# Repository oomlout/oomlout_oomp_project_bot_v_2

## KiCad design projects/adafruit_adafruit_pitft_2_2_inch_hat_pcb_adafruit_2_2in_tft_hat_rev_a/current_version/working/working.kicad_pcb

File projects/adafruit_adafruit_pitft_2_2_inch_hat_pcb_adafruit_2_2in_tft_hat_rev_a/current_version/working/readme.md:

# adafruit_pitft_2_2_inch_hat_pcb
 
## summary 
* id: adafruit_adafruit_pitft_2_2_inch_hat_pcb_adafruit_2_2in_tft_hat_rev_a
* user: adafruit
* name: adafruit_pitft_2_2_inch_hat_pcb
* board: adafruit_2_2in_tft_hat_rev_a
* repo: https://github.com/adafruit/Adafruit-PiTFT-2.2-Inch-HAT-PCB

* src_file_repo_sch: 
* src_file_repo_sch_link: https://github.com/adafruit/Adafruit-PiTFT-2.2-Inch-HAT-PCB/tree/master/
* full details link: https://github.com/oomlout/oomlout_oomp_project_bot_v_2/tree/main/projects/adafruit_adafruit_pitft_2_2_inch_hat_pcb_adafruit_2_2in_tft_hat_rev_a/current_version/working  

## schematic  
  
[schematic (pdf)](working_schematic.pdf) 

## pcb  

[board (pdf)](working.pdf)  

## working_bom
| Id | Designator | Footprint | Quantity | Designation | Supplier and ref |  | None | 
| --- | --- | --- | --- | --- | --- | --- | --- | 
| 1 | IC5 | SOT23 | 1 | AXP803 |  |  | [''] | 
| 2 | SW3,SW4,SW2,SW1 | EVQ-Q2 | 4 | SPST_TACT-EVQQ2 |  |  | [''] | 
| 3 | R2,R1,R3 | 0805-NO | 3 | 3.9K |  |  | [''] | 
| 4 | R10,R9 | 0805-NO | 2 | 1K |  |  | [''] | 
| 5 | U1 | SOIC8_150MIL | 1 | CAT24C32 |  |  | [''] | 
| 6 | RPI1 | PI_HAT_NOSLOTS | 1 | RASPBERRYPI_BPLUS_HATNOSLOTS |  |  | [''] | 
| 7 | R8,R5,R7,R4 | 0805-NO | 4 | 100 |  |  | [''] | 
| 8 | FID3,FID1,FID2 | FIDUCIAL_1MM | 3 | FIDUCIAL" |  |  | [''] | 
| 9 | U$4 | PIHATLOGO | 1 |  |  |  | [''] | 
| 10 | R6 | 0805-NO | 1 | 10K |  |  | [''] | 
| 11 | Q1 | SOT23-BEC | 1 | MMBT2222 |  |  | [''] | 
| 12 | CONN1 | 1X25_ROUND_70MIL | 1 | HEADER-1X25 |  |  | [''] | 
| 13 | U$1 | ADAFRUIT_5MM | 1 |  |  |  | [''] | 
| 14 | U2 | TM022HDH26_2.2IN_LCD | 1 | 2.2TFT |  |  | [''] | 
| 15 | U$12 | PCBFEAT-REV-056 | 1 |  |  |  | [''] | 
| 16 | SJ2 | SOLDERJUMPER_CLOSEDWIRE | 1 | BACKLITE |  |  | [''] | 
| 17 | SJ1 | SOLDERJUMPER_CLOSEDWIRE | 1 | WP |  |  | [''] | 
| 18 | U$3 | ADAFRUIT_TEXT_20MM | 1 |  |  |  | [''] | 

## bom_schematic
| Ref | Qnty | Value | Cmp name | Footprint | Description | Vendor | DNP | 
| --- | --- | --- | --- | --- | --- | --- | --- | 
| CONN1 | 1 | HEADER-1X25 | HEADER-1X25 | working:1X25_ROUND_70MIL |  |  |  | 
| FID1, FID2, FID3 | 3 | FIDUCIAL"" | FIDUCIAL{dblquote}{dblquote} | working:FIDUCIAL_1MM |  |  |  | 
| IC5 | 1 | AXP803 | AXP083-SAG | working:SOT23 |  |  |  | 
| Q1 | 1 | MMBT2222 | -NPN-SOT23-BEC | working:SOT23-BEC |  |  |  | 
| R1, R2, R3 | 3 | 3.9K | RESISTOR0805_NOOUTLINE | working:0805-NO |  |  |  | 
| R4, R5, R7, R8 | 4 | 100 | RESISTOR0805_NOOUTLINE | working:0805-NO |  |  |  | 
| R6 | 1 | 10K | RESISTOR0805_NOOUTLINE | working:0805-NO |  |  |  | 
| R9, R10 | 2 | 1K | RESISTOR0805_NOOUTLINE | working:0805-NO |  |  |  | 
| RPI1 | 1 | RASPBERRYPI_BPLUS_HATNOSLOTS | RASPBERRYPI_BPLUS_HATNOSLOTS | working:PI_HAT_NOSLOTS |  |  |  | 
| SJ1 | 1 | WP | SOLDERJUMPER_CLOSED | working:SOLDERJUMPER_CLOSEDWIRE |  |  |  | 
| SJ2 | 1 | BACKLITE | SOLDERJUMPERCLOSED | working:SOLDERJUMPER_CLOSEDWIRE |  |  |  | 
| SW1, SW2, SW3, SW4 | 4 | SPST_TACT-EVQQ2 | SPST_TACT-EVQQ2 | working:EVQ-Q2 |  |  |  | 
| U1 | 1 | CAT24C32 | EEPROM_I2C_SOIC8_GENERIC | working:SOIC8_150MIL |  |  |  | 
| U2 | 1 | 2.2TFT | DISP_LCD_TM022HDH26 | working:TM022HDH26_2.2IN_LCD |  |  |  |

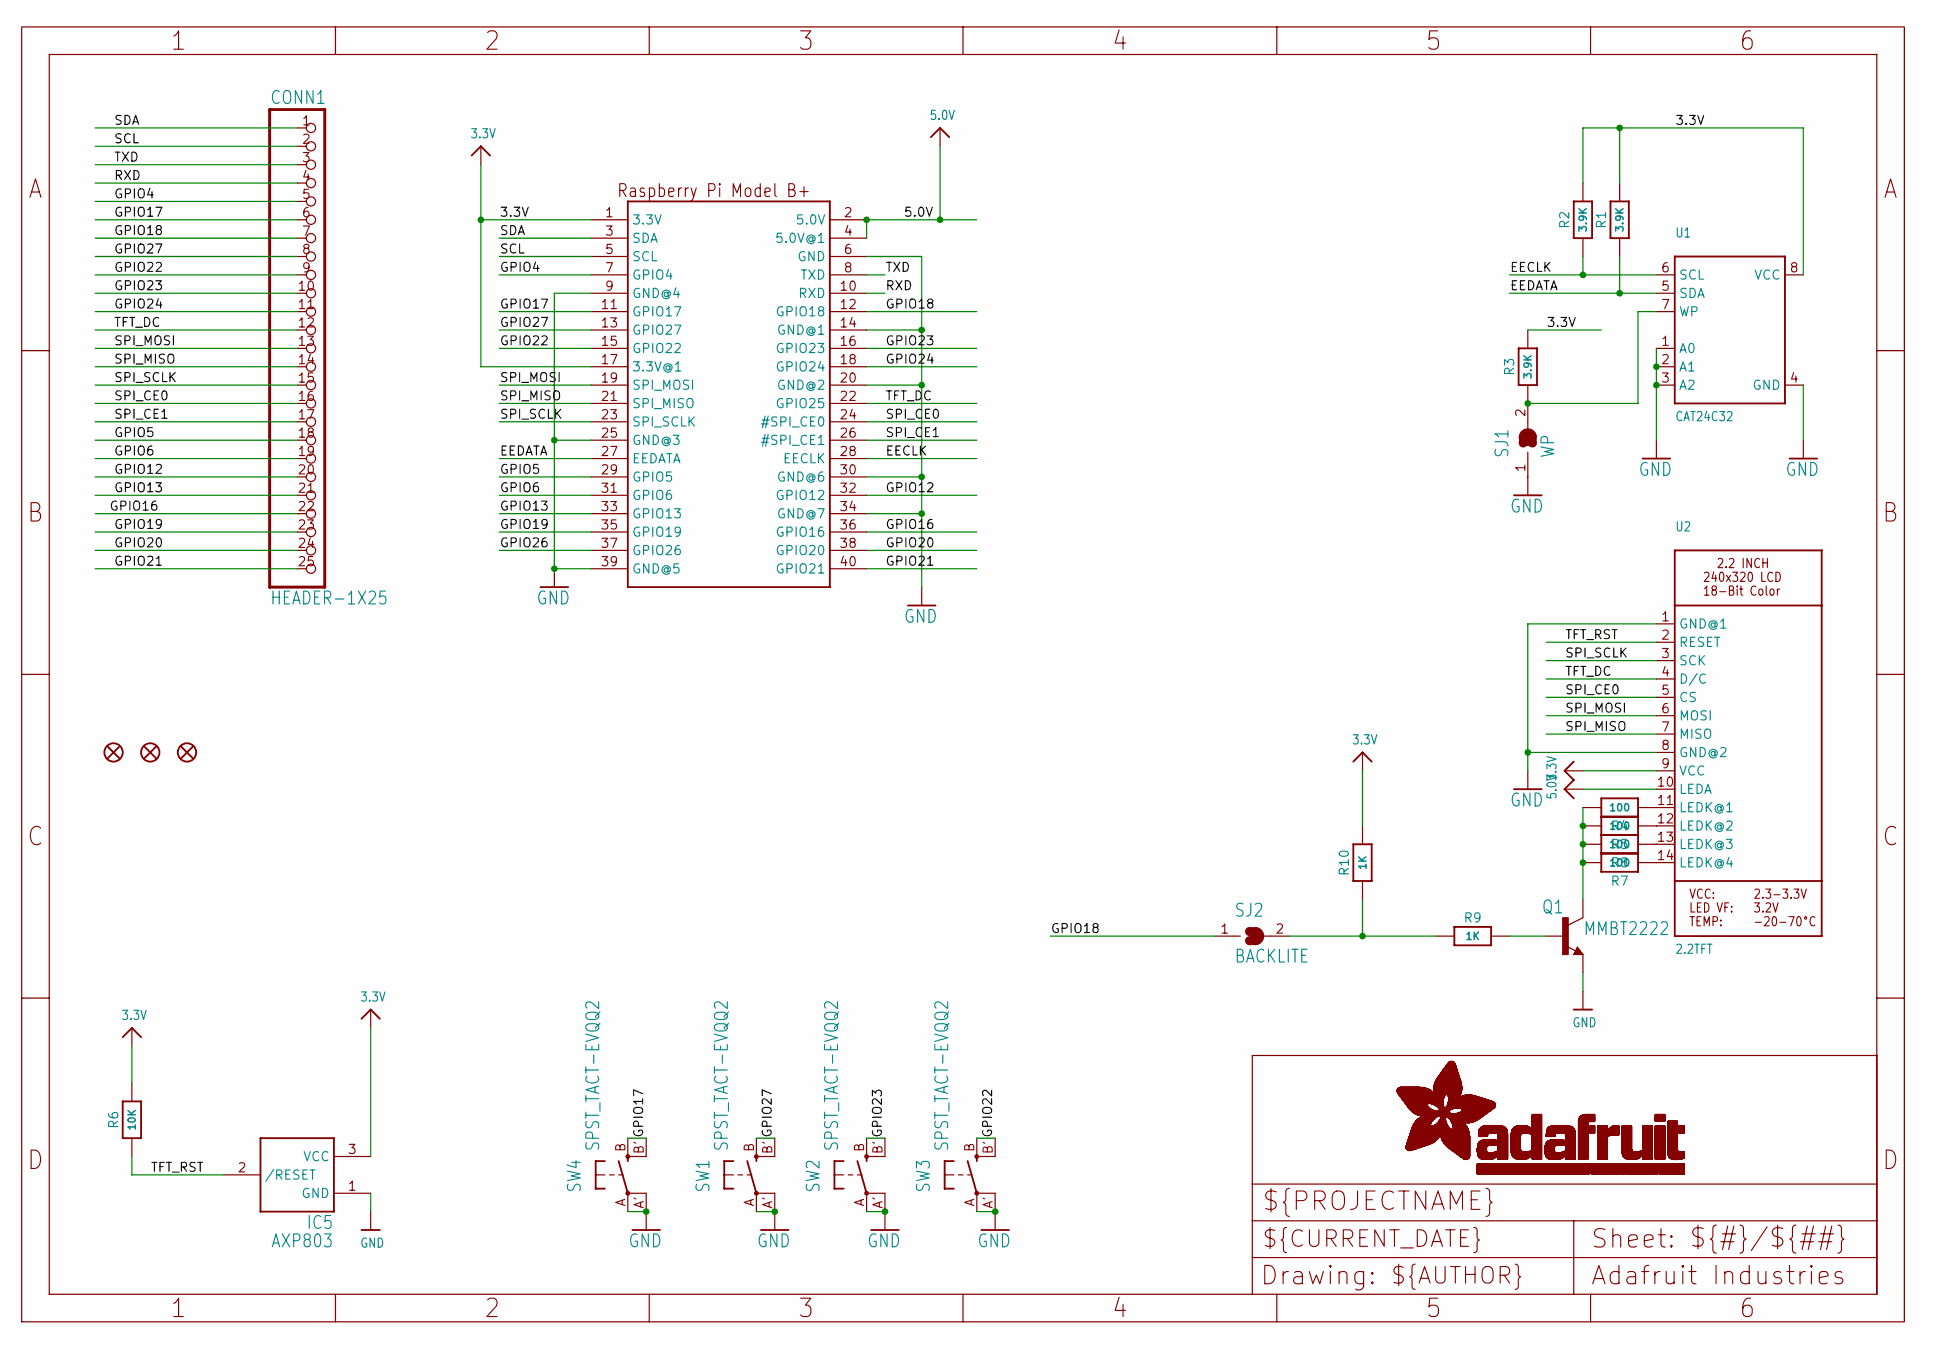
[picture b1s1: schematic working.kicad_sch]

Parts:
CONN1: HEADER-1X25; 1X25_ROUND_70MIL
FID1, FID2, FID3: FIDUCIAL""; FIDUCIAL_1MM
IC5: AXP803; SOT23
Q1: MMBT2222; SOT23-BEC
R1, R2, R3: 3.9K; 0805-NO
R4, R5, R7, R8: 100; 0805-NO
R6: 10K; 0805-NO
R9, R10: 1K; 0805-NO
RPI1: RASPBERRYPI_BPLUS_HATNOSLOTS; PI_HAT_NOSLOTS
SJ1: WP; SOLDERJUMPER_CLOSEDWIRE
SJ2: BACKLITE; SOLDERJUMPER_CLOSEDWIRE
SW1, SW2, SW3, SW4: SPST_TACT-EVQQ2; EVQ-Q2
U1: CAT24C32; SOIC8_150MIL
U2: 2.2TFT; TM022HDH26_2.2IN_LCD

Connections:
3.3V: IC5.3 (VCC), R1.2, R2.2, R3.2, R6.2, R10.2, RPI1.1 (3.3V), RPI1.17 (3.3V@1), U1.8 (VCC), U2.9 (VCC)
5.0V: RPI1.2 (5.0V), RPI1.4 (5.0V@1), U2.10 (LEDA)
EECLK: R2.1, RPI1.28 (EECLK), U1.6 (SCL)
EEDATA: R1.1, RPI1.27 (EEDATA), U1.5 (SDA)
GND: IC5.1 (GND), Q1.E, RPI1.6 (GND), RPI1.9 (GND@4), RPI1.14 (GND@1), RPI1.20 (GND@2), RPI1.25 (GND@3), RPI1.30 (GND@6), RPI1.34 (GND@7), RPI1.39 (GND@5), SJ1.1, SW1.A, SW1.A' (P1), SW2.A, SW2.A' (P1), SW3.A, SW3.A' (P1), SW4.A, SW4.A' (P1), U1.1 (A0), U1.2 (A1), U1.3 (A2), U1.4 (GND), U2.1 (GND@1), U2.8 (GND@2)
GPIO4: CONN1.5, RPI1.7 (GPIO4)
GPIO5: CONN1.18, RPI1.29 (GPIO5)
GPIO6: CONN1.19, RPI1.31 (GPIO6)
GPIO12: CONN1.20, RPI1.32 (GPIO12)
GPIO13: CONN1.21, RPI1.33 (GPIO13)
GPIO16: CONN1.22, RPI1.36 (GPIO16)
GPIO17: CONN1.6, RPI1.11 (GPIO17), SW4.B (S), SW4.B' (S1)
GPIO18: CONN1.7, RPI1.12 (GPIO18), SJ2.1
GPIO19: CONN1.23, RPI1.35 (GPIO19)
GPIO20: CONN1.24, RPI1.38 (GPIO20)
GPIO21: CONN1.25, RPI1.40 (GPIO21)
GPIO22: CONN1.9, RPI1.15 (GPIO22), SW3.B (S), SW3.B' (S1)
GPIO23: CONN1.10, RPI1.16 (GPIO23), SW2.B (S), SW2.B' (S1)
GPIO24: CONN1.11, RPI1.18 (GPIO24)
GPIO26: RPI1.37 (GPIO26)
GPIO27: CONN1.8, RPI1.13 (GPIO27), SW1.B (S), SW1.B' (S1)
unnamed: R4.1, U2.11 (LEDK@1)
unnamed: R5.1, U2.12 (LEDK@2)
unnamed: R7.1, U2.14 (LEDK@4)
unnamed: R8.1, U2.13 (LEDK@3)
unnamed: Q1.C, R4.2, R5.2, R7.2, R8.2
unnamed: Q1.B, R9.2
unnamed: R9.1, R10.1, SJ2.2
unnamed: R3.1, SJ1.2, U1.7 (WP)
RXD: CONN1.4, RPI1.10 (RXD)
SCL: CONN1.2, RPI1.5 (SCL)
SDA: CONN1.1, RPI1.3 (SDA)
SPI_CE0: CONN1.16, RPI1.24 (#SPI_CE0), U2.5 (CS)
SPI_CE1: CONN1.17, RPI1.26 (#SPI_CE1)
SPI_MISO: CONN1.14, RPI1.21 (SPI_MISO), U2.7 (MISO)
SPI_MOSI: CONN1.13, RPI1.19 (SPI_MOSI), U2.6 (MOSI)
SPI_SCLK: CONN1.15, RPI1.23 (SPI_SCLK), U2.3 (SCK)
TFT_DC: CONN1.12, RPI1.22 (GPIO25), U2.4 (D/C)
TFT_RST: IC5.2 (/RESET), R6.1, U2.2 (RESET)
TXD: CONN1.3, RPI1.8 (TXD)

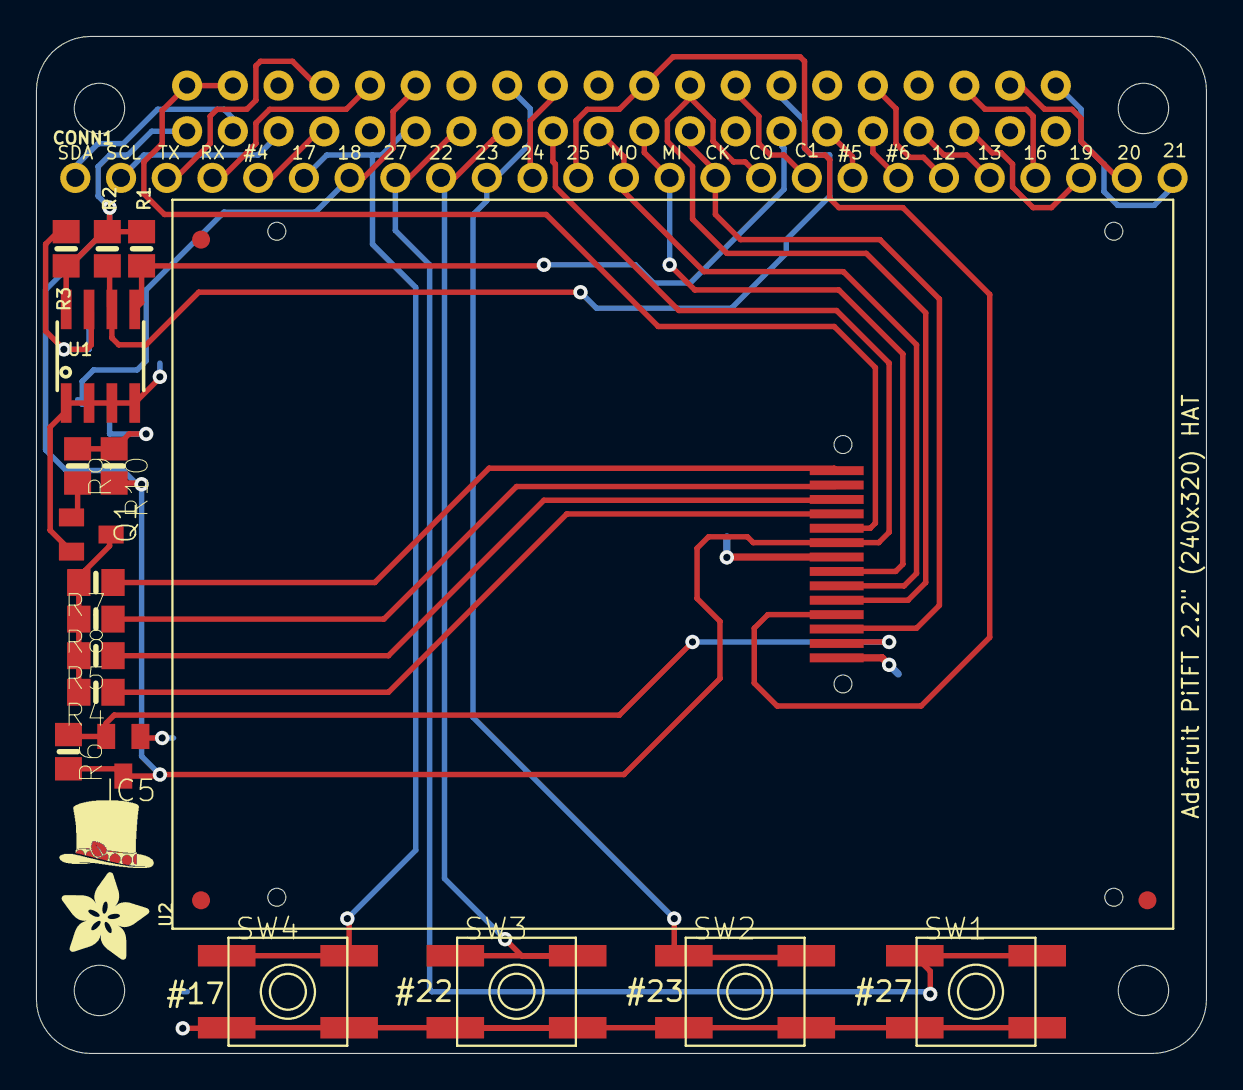
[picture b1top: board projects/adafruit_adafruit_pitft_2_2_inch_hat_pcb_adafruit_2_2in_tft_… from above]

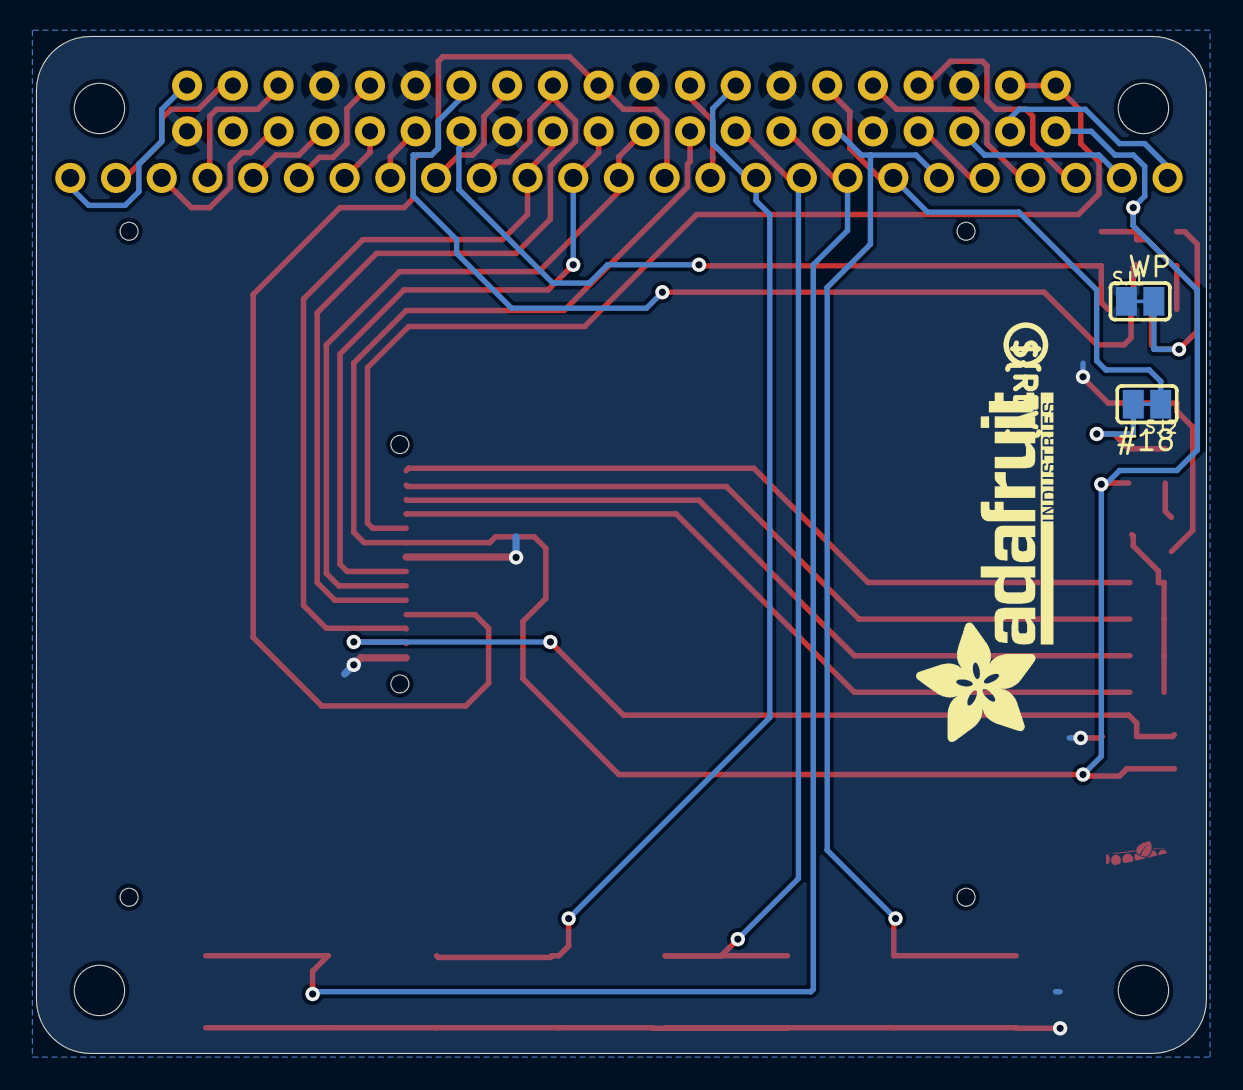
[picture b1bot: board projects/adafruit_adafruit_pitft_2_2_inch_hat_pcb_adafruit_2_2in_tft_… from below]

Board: 2 copper layers, 65.0 x 56.5 mm, 29 parts (4 on the bottom side), 39 nets.

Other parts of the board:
U$1: ADAFRUIT_5MM
U$3: ADAFRUIT_TEXT_20MM
U$4: PIHATLOGO
U$12: PCBFEAT-REV-056

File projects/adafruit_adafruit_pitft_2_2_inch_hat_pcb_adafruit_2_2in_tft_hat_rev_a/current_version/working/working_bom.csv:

"Id";"Designator";"Footprint";"Quantity";"Designation";"Supplier and ref";
1;"IC5";"SOT23";1;"AXP803";;;
2;"SW3,SW4,SW2,SW1";"EVQ-Q2";4;"SPST_TACT-EVQQ2";;;
3;"R2,R1,R3";"0805-NO";3;"3.9K";;;
4;"R10,R9";"0805-NO";2;"1K";;;
5;"U1";"SOIC8_150MIL";1;"CAT24C32";;;
6;"RPI1";"PI_HAT_NOSLOTS";1;"RASPBERRYPI_BPLUS_HATNOSLOTS";;;
7;"R8,R5,R7,R4";"0805-NO";4;"100";;;
8;"FID3,FID1,FID2";"FIDUCIAL_1MM";3;"FIDUCIAL""";;;
9;"U$4";"PIHATLOGO";1;"";;;
10;"R6";"0805-NO";1;"10K";;;
11;"Q1";"SOT23-BEC";1;"MMBT2222";;;
12;"CONN1";"1X25_ROUND_70MIL";1;"HEADER-1X25";;;
13;"U$1";"ADAFRUIT_5MM";1;"";;;
14;"U2";"TM022HDH26_2.2IN_LCD";1;"2.2TFT";;;
15;"U$12";"PCBFEAT-REV-056";1;"";;;
16;"SJ2";"SOLDERJUMPER_CLOSEDWIRE";1;"BACKLITE";;;
17;"SJ1";"SOLDERJUMPER_CLOSEDWIRE";1;"WP";;;
18;"U$3";"ADAFRUIT_TEXT_20MM";1;"";;;

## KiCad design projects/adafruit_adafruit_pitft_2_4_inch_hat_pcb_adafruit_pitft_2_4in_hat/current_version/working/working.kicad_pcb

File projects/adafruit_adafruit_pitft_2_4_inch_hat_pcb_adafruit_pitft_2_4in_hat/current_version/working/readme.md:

# adafruit_pitft_2_4_inch_hat_pcb
 
## summary 
* id: adafruit_adafruit_pitft_2_4_inch_hat_pcb_adafruit_pitft_2_4in_hat
* user: adafruit
* name: adafruit_pitft_2_4_inch_hat_pcb
* board: adafruit_pitft_2_4in_hat
* repo: https://github.com/adafruit/Adafruit-PiTFT-2.4-Inch-HAT-PCB

* src_file_repo_sch: 
* src_file_repo_sch_link: https://github.com/adafruit/Adafruit-PiTFT-2.4-Inch-HAT-PCB/tree/master/
* full details link: https://github.com/oomlout/oomlout_oomp_project_bot_v_2/tree/main/projects/adafruit_adafruit_pitft_2_4_inch_hat_pcb_adafruit_pitft_2_4in_hat/current_version/working  

## schematic  
  
[schematic (pdf)](working_schematic.pdf) 

## pcb  

[board (pdf)](working.pdf)  

## working_bom
| Id | Designator | Footprint | Quantity | Designation | Supplier and ref |  | None | 
| --- | --- | --- | --- | --- | --- | --- | --- | 
| 1 | C5,C1 | 0805-NO | 2 | 10uF |  |  | [''] | 
| 2 | R10,R11 | 0805-NO | 2 | 22 |  |  | [''] | 
| 3 | R6,R7 | 0805-NO | 2 | 10K |  |  | [''] | 
| 4 | U2 | QFN16_3MM | 1 | STMPE610 |  |  | [''] | 
| 5 | JP2 | 2X13_SMT_MALE | 1 | CID:2608 |  |  | [''] | 
| 6 | R3,R1,R4,R2 | 0805-NO | 4 | 100 |  |  | [''] | 
| 7 | R13,R12,R5,R9 | 0805-NO | 4 | 3.9K |  |  | [''] | 
| 8 | Q4 | SOT23-WIDE | 1 | BSS138 |  |  | [''] | 
| 9 | SJ1 | SOLDERJUMPER_CLOSEDWIRE | 1 | WP |  |  | [''] | 
| 10 | R8 | 0805-NO | 1 | DNP |  |  | [''] | 
| 11 | IC5 | SOT23 | 1 | AXP803 |  |  | [''] | 
| 12 | U$9 | PCBFEAT-REV-056 | 1 |  |  |  | [''] | 
| 13 | D1 | SOD-323 | 1 | 1n4148 |  |  | [''] | 
| 14 | SJ2 | SOLDERJUMPER_CLOSEDWIRE | 1 | BACKLITE |  |  | [''] | 
| 15 | U$23 | ADAFRUIT_TEXT_20MM | 1 |  |  |  | [''] | 
| 16 | U$10,U$11,U$18 | FIDUCIAL_1MM | 3 | FIDUCIAL" |  |  | [''] | 
| 17 | U1 | SOIC8_150MIL | 1 | CAT24C32 |  |  | [''] | 
| 18 | C3,C2 | 0805-NO | 2 | 0.1uF |  |  | [''] | 
| 19 | SW3,SW5,SW4,SW1,SW2 | TACT_PANA-EVQ | 5 |  |  |  | [''] | 
| 20 | RPI1 | PI_HAT_NOSLOTS | 1 | RASPBERRYPI_BPLUS_HATNOSLOTS |  |  | [''] | 
| 21 | U$2 | TFT_2.4IN_240X320_50PIN | 1 | DISP_LCD_240X320_50PIN-2.4IN |  |  | [''] | 

## bom_schematic
| Ref | Qnty | Value | Cmp name | Footprint | Description | Vendor | DNP | 
| --- | --- | --- | --- | --- | --- | --- | --- | 
| C1, C5 | 2 | 10uF | CAP_CERAMIC0805-NOOUTLINE | working:0805-NO |  |  |  | 
| C2, C3 | 2 | 0.1uF | CAP_CERAMIC0805-NOOUTLINE | working:0805-NO |  |  |  | 
| D1 | 1 | 1n4148 | DIODESOD-323 | working:SOD-323 |  |  |  | 
| IC5 | 1 | AXP803 | AXP083-SAG | working:SOT23 |  |  |  | 
| JP2 | 1 | CID:2608 | HEADER-2X13-SMT | working:2X13_SMT_MALE |  |  |  | 
| Q4 | 1 | BSS138 | MOSFET-NWIDE | working:SOT23-WIDE |  |  |  | 
| R1, R2, R3, R4 | 4 | 100 | RESISTOR0805_NOOUTLINE | working:0805-NO |  |  |  | 
| R5, R9, R12, R13 | 4 | 3.9K | RESISTOR0805_NOOUTLINE | working:0805-NO |  |  |  | 
| R6, R7 | 2 | 10K | RESISTOR0805_NOOUTLINE | working:0805-NO |  |  |  | 
| R8 | 1 | DNP | RESISTOR0805_NOOUTLINE | working:0805-NO |  |  |  | 
| R10, R11 | 2 | 22 | RESISTOR0805_NOOUTLINE | working:0805-NO |  |  |  | 
| RPI1 | 1 | RASPBERRYPI_BPLUS_HATNOSLOTS | RASPBERRYPI_BPLUS_HATNOSLOTS | working:PI_HAT_NOSLOTS |  |  |  | 
| SJ1 | 1 | WP | SOLDERJUMPER_CLOSED | working:SOLDERJUMPER_CLOSEDWIRE |  |  |  | 
| SJ2 | 1 | BACKLITE | SOLDERJUMPER_CLOSED | working:SOLDERJUMPER_CLOSEDWIRE |  |  |  | 
| SW1, SW2, SW3, SW4, SW5 | 5 | SWITCH_PUSHBUTTONEVQ-PE | SWITCH_PUSHBUTTONEVQ-PE | working:TACT_PANA-EVQ |  |  |  | 
| U1 | 1 | CAT24C32 | EEPROM_I2C_SOIC8_GENERIC | working:SOIC8_150MIL |  |  |  | 
| U2 | 1 | STMPE610 | STMPE610 | working:QFN16_3MM |  |  |  | 
| U$2 | 1 | DISP_LCD_240X320_50PIN-2.4IN | DISP_LCD_240X320_50PIN-2.4IN | working:TFT_2.4IN_240X320_50PIN |  |  |  | 
| U$10, U$11, U$18 | 3 | FIDUCIAL"" | FIDUCIAL{dblquote}{dblquote} | working:FIDUCIAL_1MM |  |  |  |

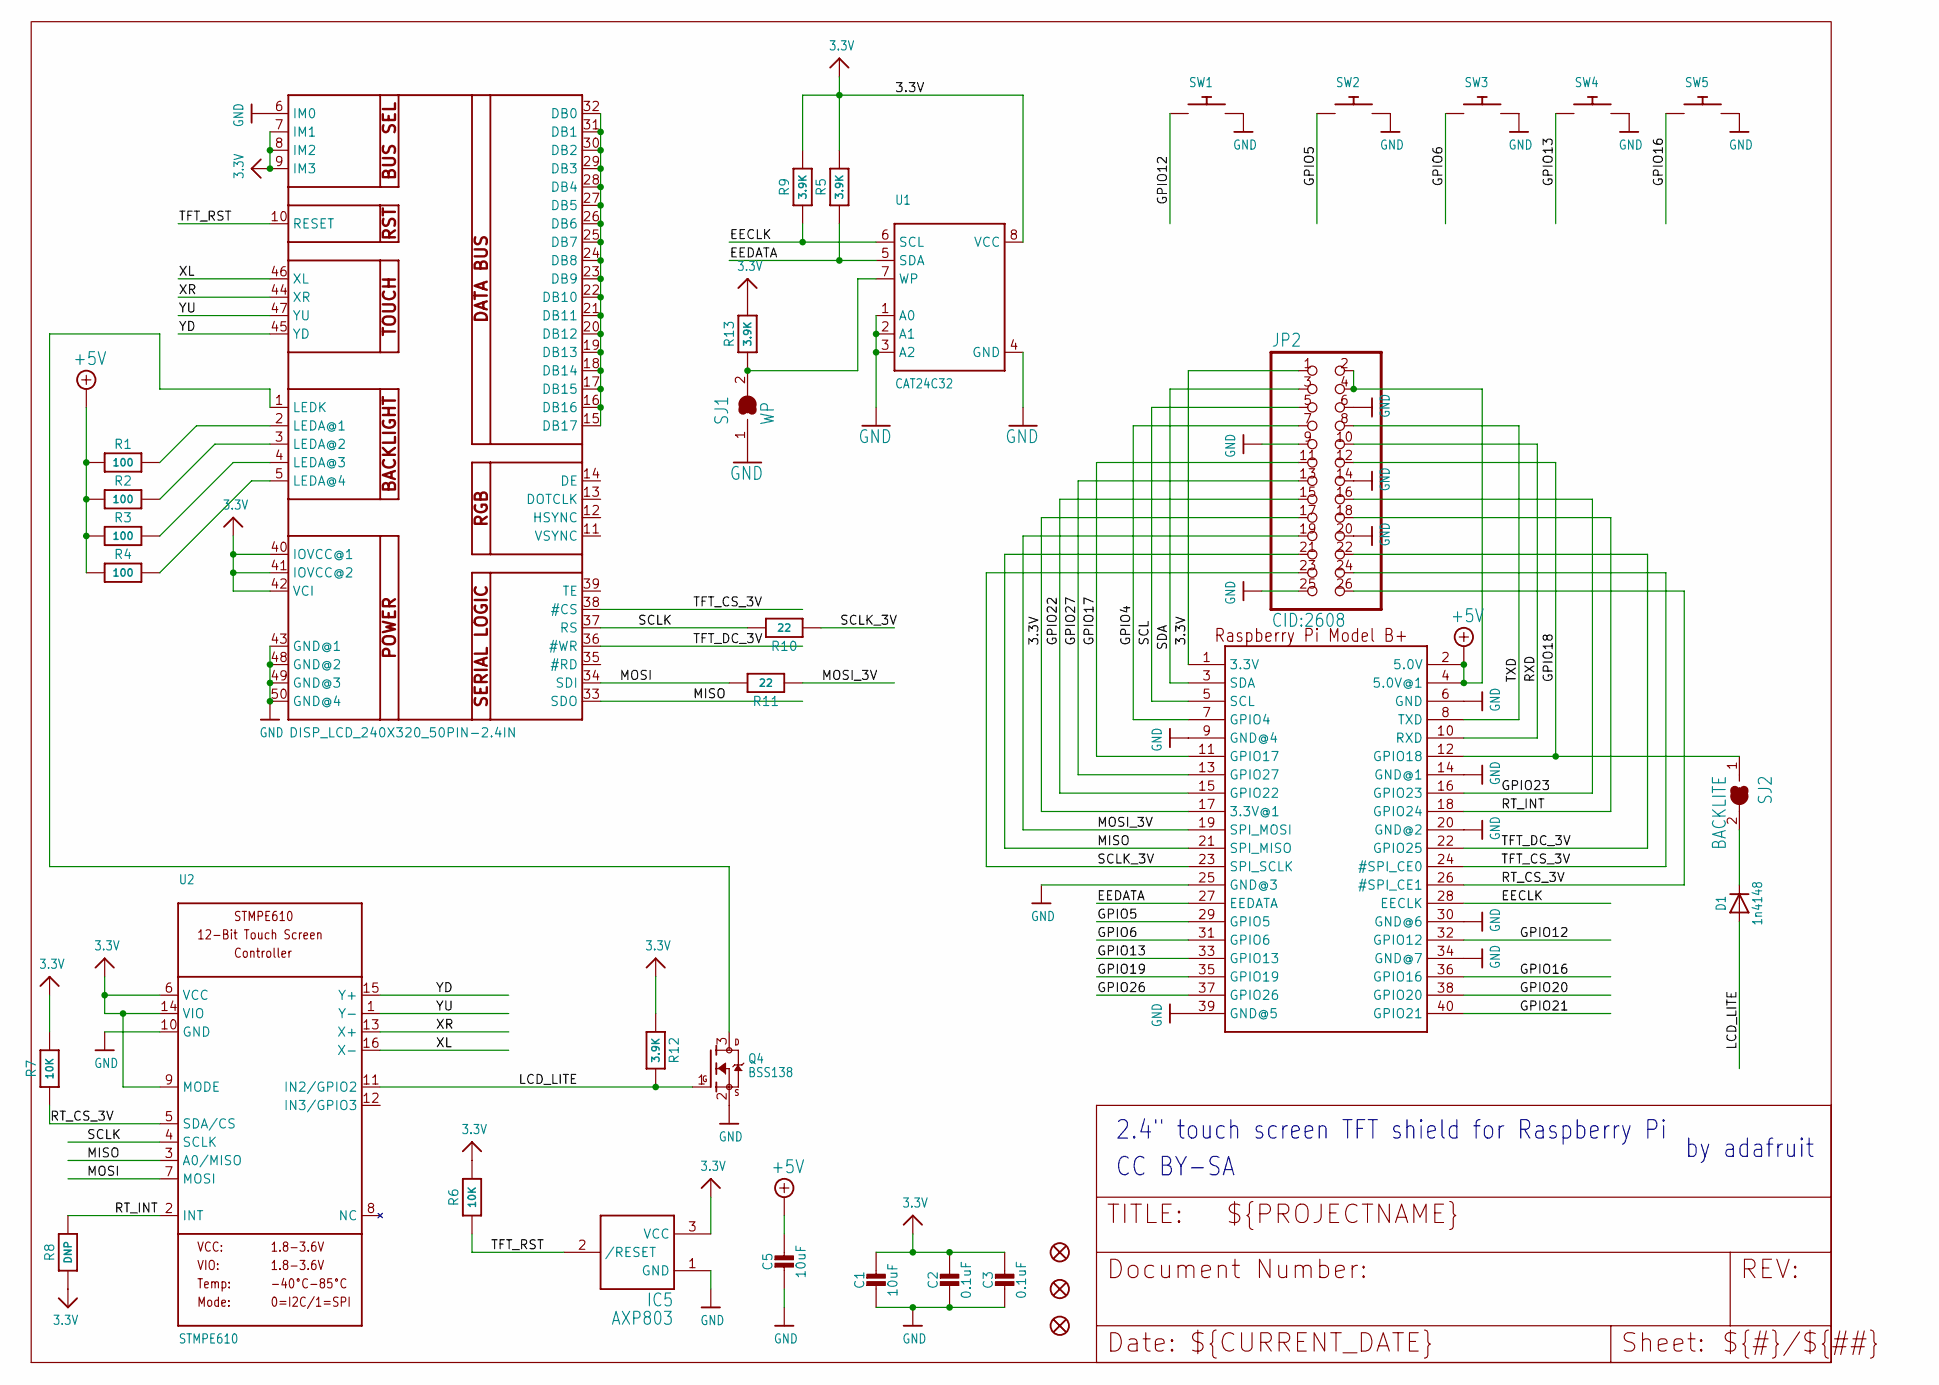
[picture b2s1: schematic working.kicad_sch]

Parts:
C1, C5: 10uF; 0805-NO
C2, C3: 0.1uF; 0805-NO
D1: 1n4148; SOD-323
IC5: AXP803; SOT23
JP2: CID:2608; 2X13_SMT_MALE
Q4: BSS138; SOT23-WIDE
R1, R2, R3, R4: 100; 0805-NO
R5, R9, R12, R13: 3.9K; 0805-NO
R6, R7: 10K; 0805-NO
R8: DNP; 0805-NO
R10, R11: 22; 0805-NO
RPI1: RASPBERRYPI_BPLUS_HATNOSLOTS; PI_HAT_NOSLOTS
SJ1: WP; SOLDERJUMPER_CLOSEDWIRE
SJ2: BACKLITE; SOLDERJUMPER_CLOSEDWIRE
SW1, SW2, SW3, SW4, SW5: SWITCH_PUSHBUTTONEVQ-PE; TACT_PANA-EVQ
U1: CAT24C32; SOIC8_150MIL
U2: STMPE610; QFN16_3MM
U$2: DISP_LCD_240X320_50PIN-2.4IN; TFT_2.4IN_240X320_50PIN
U$10, U$11, U$18: FIDUCIAL""; FIDUCIAL_1MM

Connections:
3.3V: C1.1, C2.1, C3.1, IC5.3 (VCC), JP2.1, JP2.17, R5.2, R6.2, R7.2, R8.1, R9.2, R12.1, R13.2, RPI1.1 (3.3V), RPI1.17 (3.3V@1), U1.8 (VCC), U2.6 (VCC), U2.9 (MODE), U2.14 (VIO), U$2.7 (IM1), U$2.8 (IM2), U$2.9 (IM3), U$2.40 (IOVCC@1), U$2.41 (IOVCC@2), U$2.42 (VCI)
+5V: C5.1, JP2.2, JP2.4, R1.1, R2.1, R3.1, R4.1, RPI1.2 (5.0V), RPI1.4 (5.0V@1)
EECLK: R9.1, RPI1.28 (EECLK), U1.6 (SCL)
EEDATA: R5.1, RPI1.27 (EEDATA), U1.5 (SDA)
GND: C1.2, C2.2, C3.2, C5.2, IC5.1 (GND), JP2.6, JP2.9, JP2.14, JP2.20, JP2.25, Q4.2 (S), RPI1.6 (GND), RPI1.9 (GND@4), RPI1.14 (GND@1), RPI1.20 (GND@2), RPI1.25 (GND@3), RPI1.30 (GND@6), RPI1.34 (GND@7), RPI1.39 (GND@5), SJ1.1, SW1.P$2, SW2.P$2, SW3.P$2, SW4.P$2, SW5.P$2, U1.1 (A0), U1.2 (A1), U1.3 (A2), U1.4 (GND), U2.10 (GND), U$2.6 (IM0), U$2.43 (GND@1), U$2.48 (GND@2), U$2.49 (GND@3), U$2.50 (GND@4)
GPIO4: JP2.7, RPI1.7 (GPIO4)
GPIO5: RPI1.29 (GPIO5), SW2.P$1
GPIO6: RPI1.31 (GPIO6), SW3.P$1
GPIO12: RPI1.32 (GPIO12), SW1.P$1
GPIO13: RPI1.33 (GPIO13), SW4.P$1
GPIO16: RPI1.36 (GPIO16), SW5.P$1
GPIO17: JP2.11, RPI1.11 (GPIO17)
GPIO18: JP2.12, RPI1.12 (GPIO18), SJ2.1
GPIO19: RPI1.35 (GPIO19)
GPIO20: RPI1.38 (GPIO20)
GPIO21: RPI1.40 (GPIO21)
GPIO22: JP2.15, RPI1.15 (GPIO22)
GPIO23: JP2.16, RPI1.16 (GPIO23)
GPIO26: RPI1.37 (GPIO26)
GPIO27: JP2.13, RPI1.13 (GPIO27)
LCD_LITE: D1.A, Q4.1 (G), R12.2, U2.11 (IN2/GPIO2)
MISO: JP2.21, RPI1.21 (SPI_MISO), U2.3 (A0/MISO), U$2.33 (SDO)
MOSI: R11.2, U2.7 (MOSI), U$2.34 (SDI)
MOSI_3V: JP2.19, R11.1, RPI1.19 (SPI_MOSI)
unnamed: R1.2, U$2.2 (LEDA@1)
unnamed: R2.2, U$2.3 (LEDA@2)
unnamed: R3.2, U$2.4 (LEDA@3)
unnamed: Q4.3 (D), U$2.1 (LEDK)
unnamed: D1.C, SJ2.2
unnamed: U$2.15 (DB17), U$2.16 (DB16), U$2.17 (DB15), U$2.18 (DB14), U$2.19 (DB13), U$2.20 (DB12), U$2.21 (DB11), U$2.22 (DB10), U$2.23 (DB9), U$2.24 (DB8), U$2.25 (DB7), U$2.26 (DB6), U$2.27 (DB5), U$2.28 (DB4), U$2.29 (DB3), U$2.30 (DB2), U$2.31 (DB1), U$2.32 (DB0)
unnamed: R4.2, U$2.5 (LEDA@4)
unnamed: R13.1, SJ1.2, U1.7 (WP)
RT_CS_3V: JP2.26, R7.1, RPI1.26 (#SPI_CE1), U2.5 (SDA/CS)
RT_INT: JP2.18, R8.2, RPI1.18 (GPIO24), U2.2 (INT)
RXD: JP2.10, RPI1.10 (RXD)
SCL: JP2.5, RPI1.5 (SCL)
SCLK: R10.2, U2.4 (SCLK), U$2.37 (RS)
SCLK_3V: JP2.23, R10.1, RPI1.23 (SPI_SCLK)
SDA: JP2.3, RPI1.3 (SDA)
TFT_CS_3V: JP2.24, RPI1.24 (#SPI_CE0), U$2.38 (#CS)
TFT_DC_3V: JP2.22, RPI1.22 (GPIO25), U$2.36 (#WR)
TFT_RST: IC5.2 (/RESET), R6.1, U$2.10 (RESET)
TXD: JP2.8, RPI1.8 (TXD)
XL: U2.16 (X-), U$2.46 (XL)
XR: U2.13 (X+), U$2.44 (XR)
YD: U2.15 (Y+), U$2.45 (YD)
YU: U2.1 (Y-), U$2.47 (YU)

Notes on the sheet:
CC BY-SA
2.4" touch screen TFT shield for Raspberry Pi
by adafruit~{}

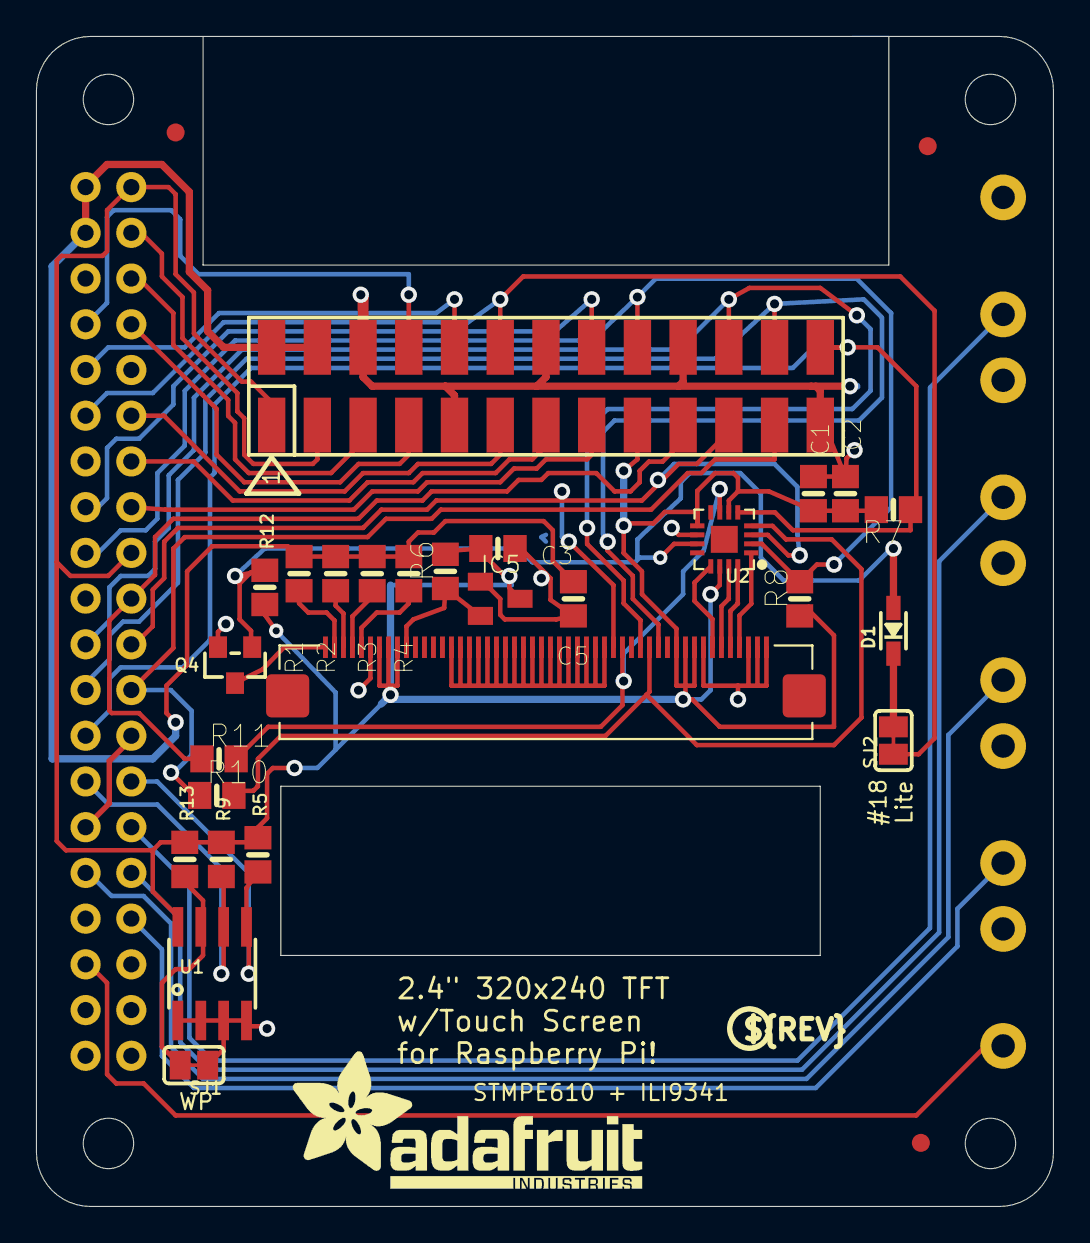
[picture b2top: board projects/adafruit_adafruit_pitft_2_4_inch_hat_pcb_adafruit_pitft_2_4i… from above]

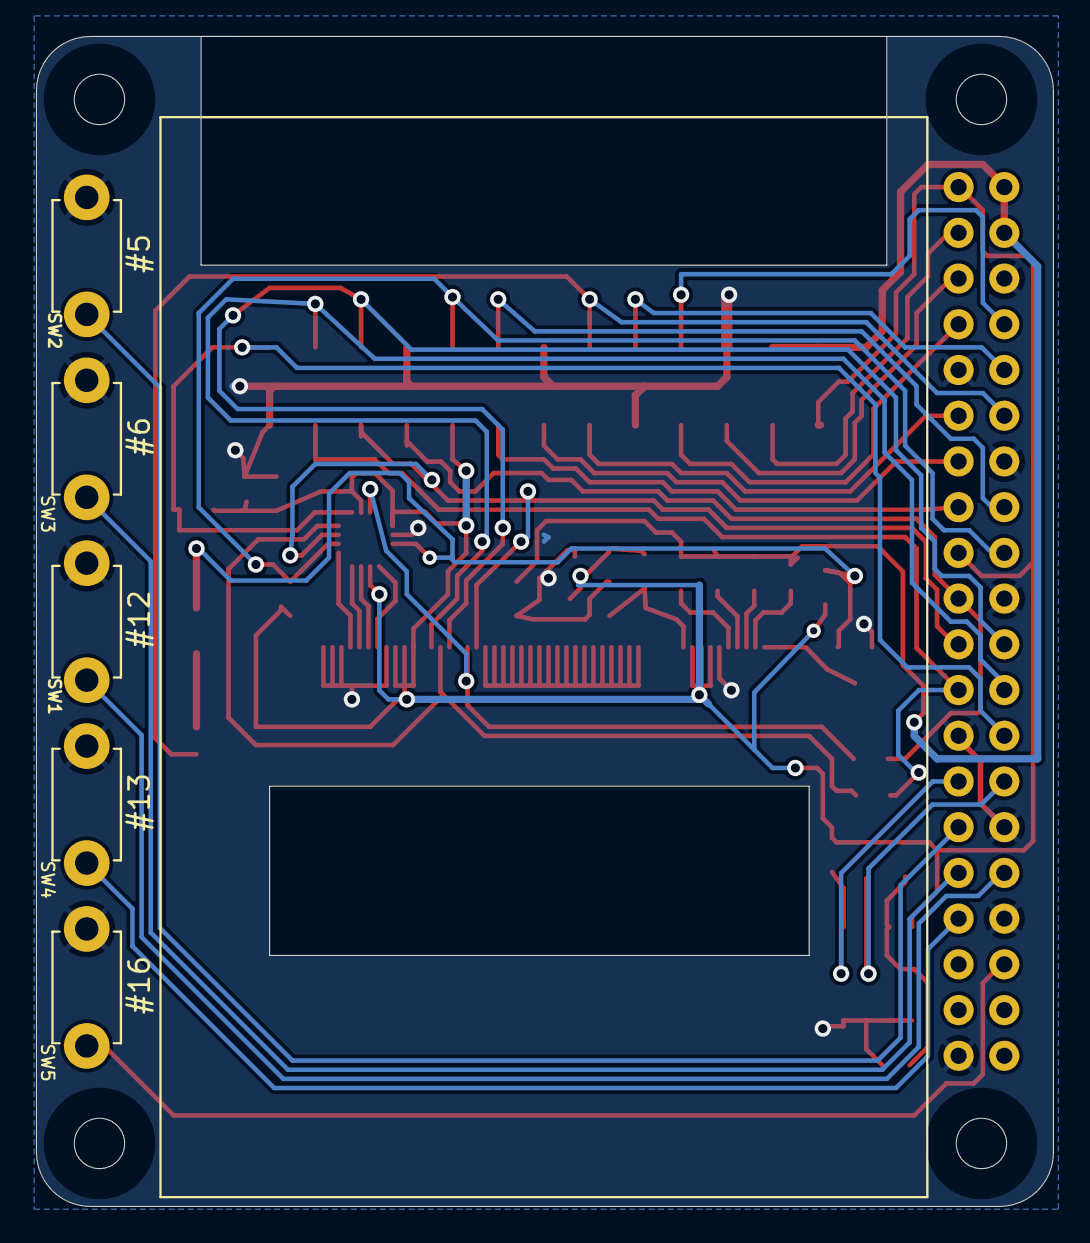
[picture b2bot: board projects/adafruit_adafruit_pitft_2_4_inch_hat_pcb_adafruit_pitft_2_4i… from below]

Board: 16 copper layers, 56.5 x 65.0 mm, 37 parts (7 on the bottom side), 43 nets.

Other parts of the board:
U$9: PCBFEAT-REV-056
U$23: ADAFRUIT_TEXT_20MM

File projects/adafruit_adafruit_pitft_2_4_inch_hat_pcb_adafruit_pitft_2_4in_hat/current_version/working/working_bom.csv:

"Id";"Designator";"Footprint";"Quantity";"Designation";"Supplier and ref";
1;"C5,C1";"0805-NO";2;"10uF";;;
2;"R10,R11";"0805-NO";2;"22";;;
3;"R6,R7";"0805-NO";2;"10K";;;
4;"U2";"QFN16_3MM";1;"STMPE610";;;
5;"JP2";"2X13_SMT_MALE";1;"CID:2608";;;
6;"R3,R1,R4,R2";"0805-NO";4;"100";;;
7;"R13,R12,R5,R9";"0805-NO";4;"3.9K";;;
8;"Q4";"SOT23-WIDE";1;"BSS138";;;
9;"SJ1";"SOLDERJUMPER_CLOSEDWIRE";1;"WP";;;
10;"R8";"0805-NO";1;"DNP";;;
11;"IC5";"SOT23";1;"AXP803";;;
12;"U$9";"PCBFEAT-REV-056";1;"";;;
13;"D1";"SOD-323";1;"1n4148";;;
14;"SJ2";"SOLDERJUMPER_CLOSEDWIRE";1;"BACKLITE";;;
15;"U$23";"ADAFRUIT_TEXT_20MM";1;"";;;
16;"U$10,U$11,U$18";"FIDUCIAL_1MM";3;"FIDUCIAL""";;;
17;"U1";"SOIC8_150MIL";1;"CAT24C32";;;
18;"C3,C2";"0805-NO";2;"0.1uF";;;
19;"SW3,SW5,SW4,SW1,SW2";"TACT_PANA-EVQ";5;"";;;
20;"RPI1";"PI_HAT_NOSLOTS";1;"RASPBERRYPI_BPLUS_HATNOSLOTS";;;
21;"U$2";"TFT_2.4IN_240X320_50PIN";1;"DISP_LCD_240X320_50PIN-2.4IN";;;
